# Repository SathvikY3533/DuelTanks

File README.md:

# Duel Tanks
### Two-player real-time tank battle — ECE319H Spring 2026

> Check out more of my work at **[sathvikyechuri.com](https://www.sathvikyechuri.com)**

---

## Demo

📺 *Video coming soon*

---

## Screenshots

| Splash Screen | Tank Select | Gameplay |
|---|---|---|
| *coming soon* | *coming soon* | *coming soon* |

---

## Overview

Duel Tanks is a real-time two-player artillery game built completely from scratch on the MSPM0G3507 microcontroller. Two players face off on separate boards connected by a UART link — shells fired off one screen physically cross over to the opponent's screen, with full parabolic physics preserved across the wire.

Everything — the graphics engine, sprite system, physics engine, UART protocol, sound system, and game state machine — was written from scratch in C++. No game engine, no external libraries.

**Placed 3rd in the ECE319H Spring 2026 in-class competition.**

---

## How It Works

Each board runs the same firmware with a `PLAYER_ID` flag determining which side the player starts on. Missiles exit one screen, get encoded into a 5-byte UART packet, and spawn on the opponent's screen with matching velocity — making it feel like a single continuous battlefield split across two displays.

```
Board 1 (left)          Board 2 (right)
┌──────────────┐        ┌──────────────┐
│   🎯   >>>   │──UART──│   >>> 💥     │
│  [Tank]      │        │       [Tank] │
└──────────────┘        └──────────────┘
     PA8 TX ──────────────► PA22 RX
     PA22 RX ◄────────────── PA8 TX
     GND ◄──────────────────► GND
```

---

## Features

- **Parabolic missile physics** — fixed-point arithmetic, gravity simulation, arc trajectory
- **Cross-screen projectiles** — missiles exit your screen and appear on the opponent's via UART
- **City background** — night skyline with building silhouettes and window lighting
- **Hilly terrain** — multi-sine generated terrain profile, tanks ride the hills
- **3 playable tanks** with unique abilities:
  - 🔵 **Brawler** — Double Shot (fires two missiles spread ±5°)
  - 🟢 **Phantom** — Speed Boost (2× movement speed for 1.5 sec)
  - 🔴 **Artillery** — Ricochet (next shot bounces off terrain)
- **Full game flow** — splash → language select → rules → tank select → battle ready handshake → countdown → gameplay → end screen
- **2-minute match timer** — compare lives at time's up for winner
- **English / Spanish** language support
- **Sound effects** — shoot, explosion, incoming warning, victory, defeat, and more

---

## Hardware

| Component | Details |
|---|---|
| MCU | MSPM0G3507 LaunchPad |
| Display | ST7735R LCD (160×128, landscape) |
| Input | 4 tactile buttons + slide potentiometer |
| Audio | 5-bit R2R DAC → MCP34119P amplifier → speaker |
| Sync | Battle Ready GPIO handshake (PA17 / PA31) |
| Communication | UART at 115200 baud, board-to-board |

### Pin Map
| Signal | Pin |
|---|---|
| LCD SPI | PB6, PB7, PB8, PB9, PB15, PA13 |
| Slide pot (ADC) | PB18 |
| 5-bit DAC | PB0 – PB4 |
| UART TX | PA8 (UART1) |
| UART RX | PA22 (UART2) |
| Battle Ready Out | PA17 (P1) / PA31 (P2) |
| Battle Ready In | PA31 (P1) / PA17 (P2) |
| Fire button | PB17 |
| Shield button | PB12 |
| Left button | PB16 |
| Right button | PA27 |

---

## Software Architecture

```
main5.cpp
└── Game_Update()          ← called every 33ms (30Hz)
    ├── Switch_Tick()      ← edge detection for all 4 buttons
    ├── State machine      ← SPLASH → LANGUAGE → RULES → TANK_SELECT
    │                         → WAITING → COUNTDOWN → GAMEPLAY → END
    ├── Physics engine     ← fixed-point parabolic missile simulation
    ├── Sprite renderer    ← transparent pixel-by-pixel draw, dirty-rect erase
    ├── GameUART           ← 5-byte packets with 0xAA 0x55 sync header
    └── Sound engine       ← SysTick ISR at 11025Hz → R2R DAC output
```

### UART Packet Format
```
[ 0xAA ][ 0x55 ][ TYPE ][ DATA1 ][ DATA2 ]
  sync    sync    what    payload  payload
```

---

## Controls

| Input | Action |
|---|---|
| Left / Right buttons | Move tank |
| Slide pot | Aim angle (0° – 89°) |
| Hold Fire | Charge shot power |
| Release Fire | Shoot |
| Shield | Use tank ability |
| Fire + Left + Right (hold) | Force quit match |

---

## Building

Open in Code Composer Studio with the ECE319H Lab 9 starter project. Add all `.cpp` / `.h` files. Before flashing:

1. Set `#define PLAYER_ID 1` in `Game.h` for the left board
2. Set `#define PLAYER_ID 2` in `Game.h` for the right board
3. Connect boards: PA8→PA22, PA22→PA8, GND→GND

---

## License

Built for ECE319H at UT Austin. All game logic, physics, graphics, and UART protocol written from scratch.

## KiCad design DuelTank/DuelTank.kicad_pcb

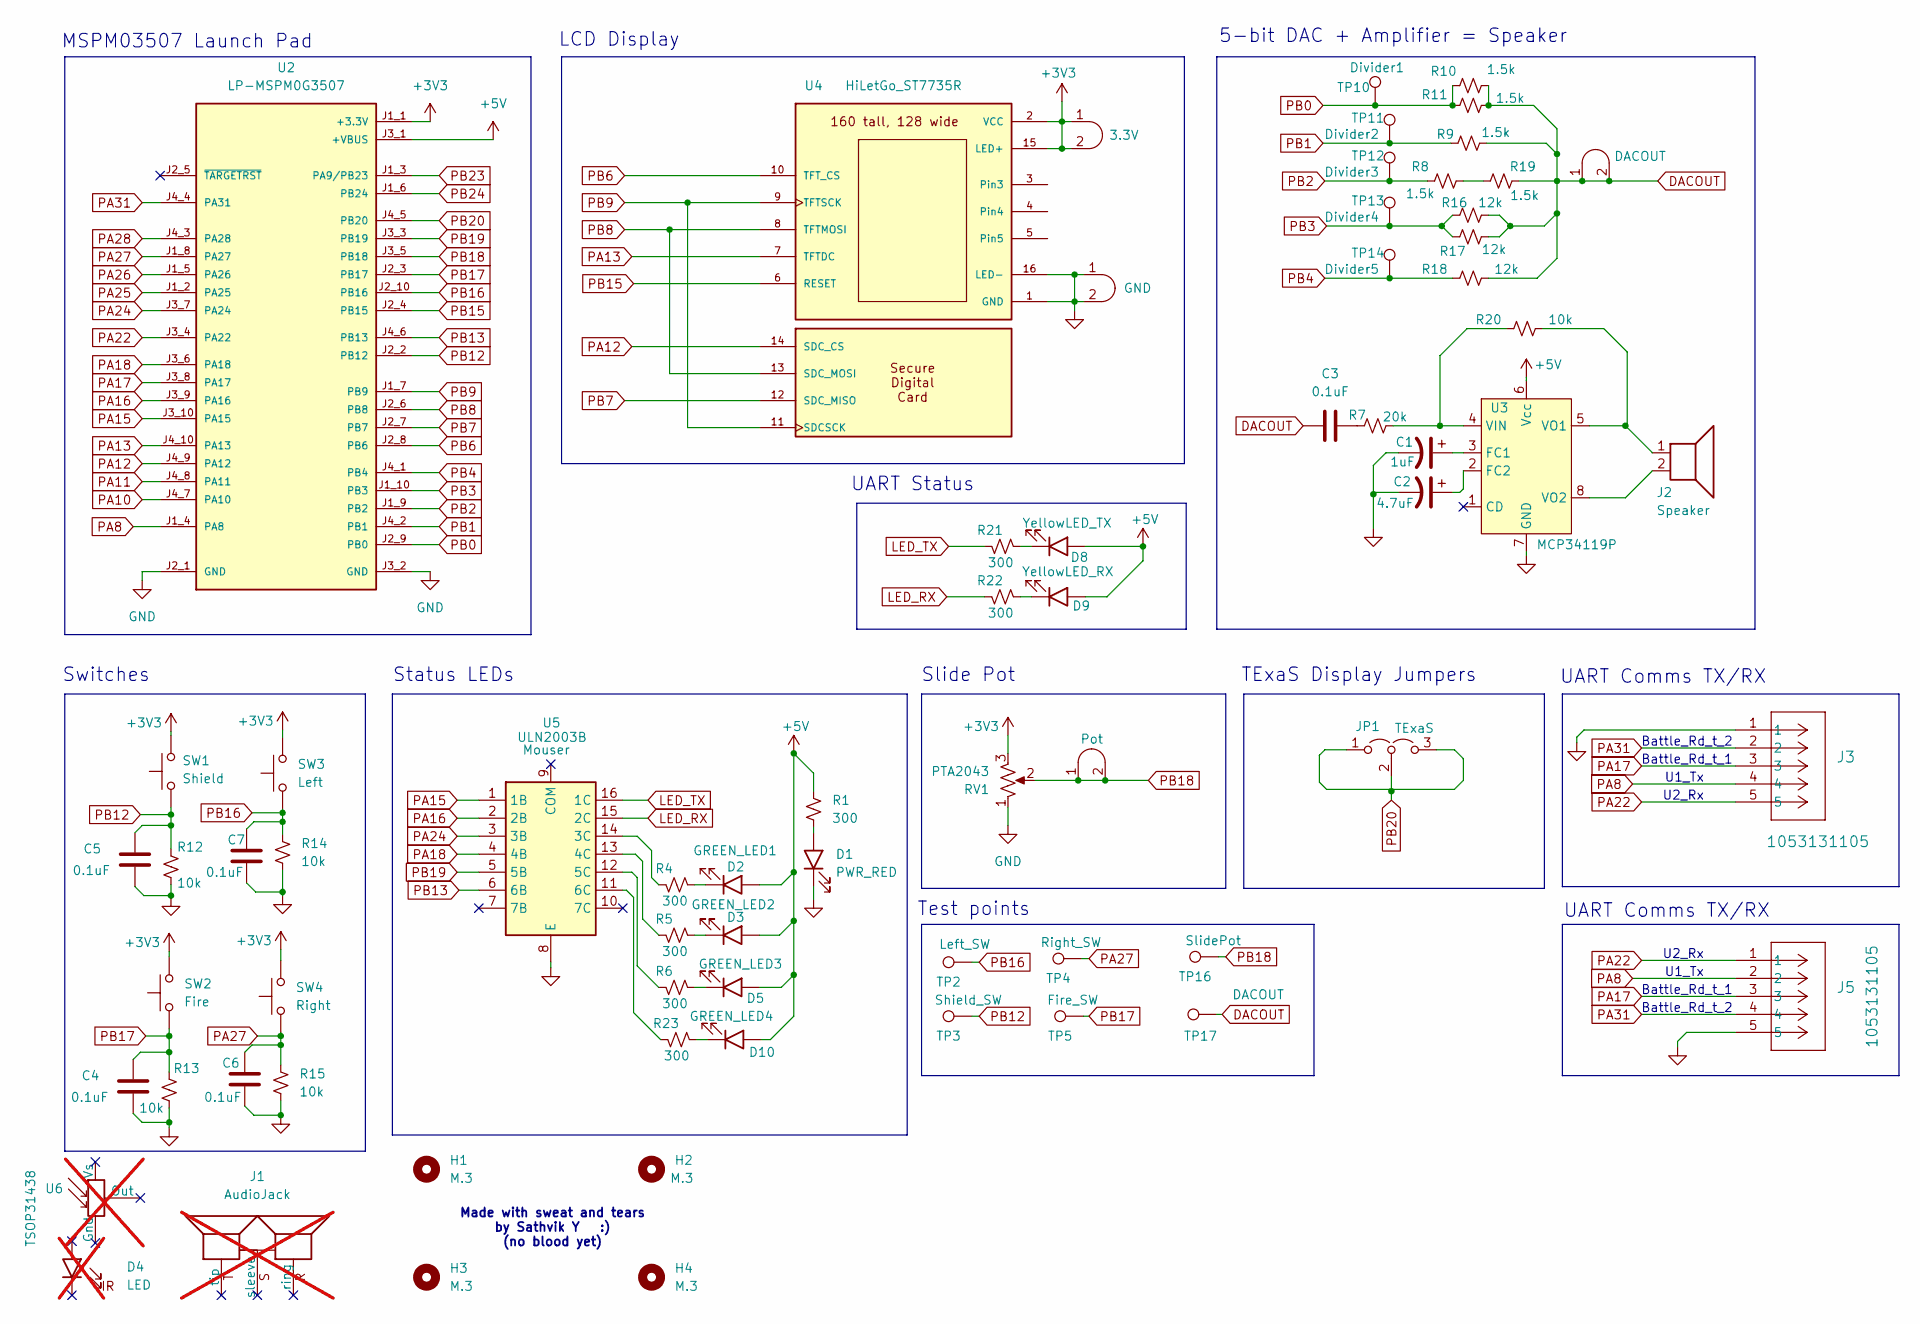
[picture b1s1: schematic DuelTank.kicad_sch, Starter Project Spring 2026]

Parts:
C1: 1uF; CP_Radial_Tantal200mil
C2: 4.7uF; CP_Radial_Tantal200mil
C3, C4, C5, C6, C7: 0.1uF; C_Axial_200mil
D1: PWR_RED; LED_D5.0mm
D2: GREEN_LED1; LED_D5.0mm
D3: GREEN_LED2; LED_D5.0mm
D4: LED; LED_D5.0mm; not fitted
D5: GREEN_LED3; LED_D5.0mm
D8: YellowLED_TX; LED_D5.0mm
D9: YellowLED_RX; LED_D5.0mm
D10: GREEN_LED4; LED_D5.0mm
H1, H2, H3, H4: M.3; MountingHole_3.2mm_M3_Pad_TopBottom
J1: AudioJack; Jack_3.5mm_CUI_SJ1-3523N_Horizontal; not fitted
J2: Speaker; PinHeader_1x02_P2.54mm_Vertical
J3, J5: 1053131105; CONN_SD-105313-100_05_MOL
J4: Pot; Testpoint_1x02_P2.54mm
J6: GND; Testpoint_1x02_P2.54mm
J7: DACOUT; Testpoint_1x02_P2.54mm
JP1: TExaS; PinHeader_1x03_P2.54mm_Vertical
R1, R4, R5, R6, R21, R22, R23: 300; R_Axial_DIN0204_L3.6mm_D1.6mm_P7.62mm_Horizontal
R7: 20k; R_Axial_DIN0204_L3.6mm_D1.6mm_P7.62mm_Horizontal
R8, R9, R10, R11, R19: 1.5k; R_Axial_DIN0204_L3.6mm_D1.6mm_P7.62mm_Horizontal
R12, R13, R14, R15, R20: 10k; R_Axial_DIN0204_L3.6mm_D1.6mm_P7.62mm_Horizontal
R16, R17, R18: 12k; R_Axial_DIN0204_L3.6mm_D1.6mm_P7.62mm_Horizontal
RV1: PTA2043; PTA2043pot
SW1: Shield; SW_PUSH_6mm
SW2: Fire; SW_PUSH_6mm
SW3: Left; SW_PUSH_6mm
SW4: Right; SW_PUSH_6mm
TP1: 3.3V; Testpoint_1x02_P2.54mm
TP2: Left_SW; TestPoint_Pad_D2.0mm
TP3: Shield_SW; TestPoint_Pad_D2.0mm
TP4: Right_SW; TestPoint_Pad_D2.0mm
TP5: Fire_SW; TestPoint_Pad_D2.0mm
TP10: Divider1; TestPoint_Pad_D2.0mm
TP11: Divider2; TestPoint_Pad_D2.0mm
TP12: Divider3; TestPoint_Pad_D2.0mm
TP13: Divider4; TestPoint_Pad_D2.0mm
TP14: Divider5; TestPoint_Pad_D2.0mm
TP16: SlidePot; TestPoint_Pad_D2.0mm
TP17: DACOUT; TestPoint_Pad_D2.0mm
U2: LP-MSPM0G3507; ti_LP_MSPM0G3507
U3: MCP34119P; DIP-8_W7.62mm_LongPads
U4: HiLetGo_ST7735R; hiletgo_st7735r
U5: ULN2003B; DIP-16_W7.62mm
U6: TSOP31438; not fitted

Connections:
+3V3: RV1.3, SW1.2, SW2.2, SW3.2, SW4.2, TP1.1 (A), TP1.2 (B), U2.J1_1 (+3.3V), U4.2 (VCC), U4.15 (LED+); also elsewhere on the board
+5V: D2.2 (A), D3.2 (A), D5.2 (A), D8.2 (A), D9.2 (A), D10.2 (A), R1.1, U2.J3_1 (+VBUS), U3.6 (Vcc)
DACOUT: C3.1, J7.1 (A), J7.2 (B), R9.1, R10.1, R11.1, R16.1, R17.1, R18.1, R19.1, TP17.1
GND: C1.2, C2.2, C4.1, C5.1, C6.1, C7.1, D1.1 (K), J3.1, J5.5, J6.1 (A), J6.2 (B), R12.2, R13.2, R14.2, R15.2, RV1.1, U2.J2_1 (GND), U2.J3_2 (GND), U3.7 (GND), U4.1 (GND), U4.16 (LED-), U5.8 (E); also elsewhere on the board
LED_RX: R22.2, U5.15 (2C)
LED_TX: R21.2, U5.16 (1C)
unnamed: C3.2, R7.2
unnamed: D1.2 (A), R1.2
unnamed: D2.1 (K), R4.1
unnamed: D3.1 (K), R5.1
unnamed: D5.1 (K), R6.1
unnamed: D8.1 (K), R21.1
unnamed: D9.1 (K), R22.1
unnamed: D10.1 (K), R23.1
unnamed: R8.1, R19.2
unnamed: C1.1, U3.3 (FC1)
unnamed: C2.1, U3.2 (FC2)
unnamed: R7.1, R20.2, U3.4 (VIN)
unnamed: J2.1, R20.1, U3.5 (VO1)
unnamed: J2.2, U3.8 (VO2)
unnamed: R4.2, U5.14 (3C)
unnamed: R5.2, U5.13 (4C)
unnamed: R6.2, U5.12 (5C)
unnamed: R23.2, U5.11 (6C)
PA8: J3.4, J5.2, U2.J1_4 (PA8)
PA10: U2.J4_7 (PA10)
PA11: U2.J4_8 (PA11)
PA12: U2.J4_9 (PA12), U4.14 (SDC_CS)
PA13: U2.J4_10 (PA13), U4.7 (TFTDC); also elsewhere on the board
PA15: U2.J3_10 (PA15), U5.1 (1B)
PA16: U2.J3_9 (PA16), U5.2 (2B)
PA17: J3.3, J5.3, U2.J3_8 (PA17)
PA18: U2.J3_6 (PA18), U5.4 (4B)
PA22: J3.5, J5.1, U2.J3_4 (PA22)
PA24: U2.J3_7 (PA24), U5.3 (3B)
PA25: U2.J1_2 (PA25)
PA26: U2.J1_5 (PA26)
PA27: C6.2, R15.1, SW4.1, TP4.1, U2.J1_8 (PA27)
PA28: U2.J4_3 (PA28)
PA31: J3.2, J5.4, U2.J4_4 (PA31)
PB0: R10.2, R11.2, TP10.1, U2.J2_9 (PB0)
PB1: R9.2, TP11.1, U2.J4_2 (PB1)
PB2: R8.2, TP12.1, U2.J1_9 (PB2)
PB3: R16.2, R17.2, TP13.1, U2.J1_10 (PB3)
PB4: R18.2, TP14.1, U2.J4_1 (PB4)
PB6: U2.J2_8 (PB6), U4.10 (TFT_CS); also elsewhere on the board
PB7: U2.J2_7 (PB7), U4.12 (SDC_MISO)
PB8: U2.J2_6 (PB8), U4.8 (TFTMOSI), U4.13 (SDC_MOSI); also elsewhere on the board
PB9: U2.J1_7 (PB9), U4.9 (TFTSCK), U4.11 (SDCSCK); also elsewhere on the board
PB12: C5.2, R12.1, SW1.1, TP3.1, U2.J2_2 (PB12)
PB13: U2.J4_6 (PB13), U5.6 (6B)
PB15: U2.J2_4 (PB15), U4.6 (RESET); also elsewhere on the board
PB16: C7.2, R14.1, SW3.1, TP2.1, U2.J2_10 (PB16)
PB17: C4.2, R13.1, SW2.1, TP5.1, U2.J2_3 (PB17)
PB18: J4.1 (A), J4.2 (B), RV1.2, TP16.1, U2.J3_5 (PB18)
PB19: U2.J3_3 (PB19), U5.5 (5B)
PB20: JP1.1 (A), JP1.2 (C), JP1.3 (B), U2.J4_5 (PB20)
PB23: U2.J1_3 (PA9/PB23)
PB24: U2.J1_6 (PB24)

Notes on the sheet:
Battle_Rd_t_1
LCD Display
U1_Tx
Battle_Rd_t_2
U2_Rx
5-bit DAC + Amplifier = Speaker
TExaS Display Jumpers
Slide Pot
Test points
Switches
Status LEDs
MSPM03507 Launch Pad
UART Comms TX/RX
Made with sweat and tears by Sathvik Y :) (no blood yet)
UART Status

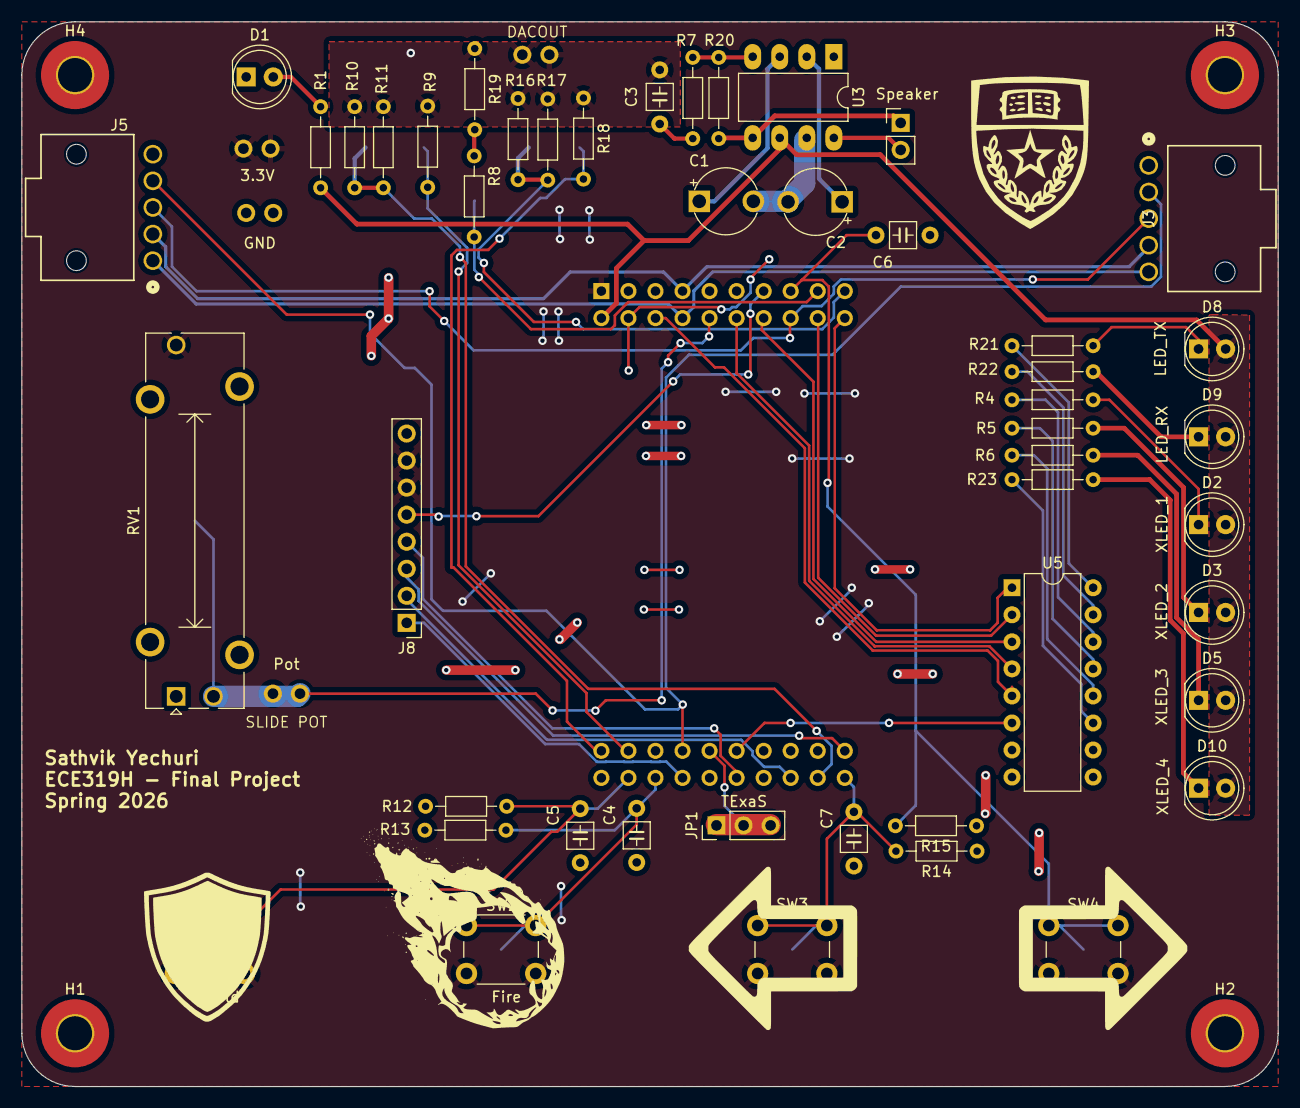
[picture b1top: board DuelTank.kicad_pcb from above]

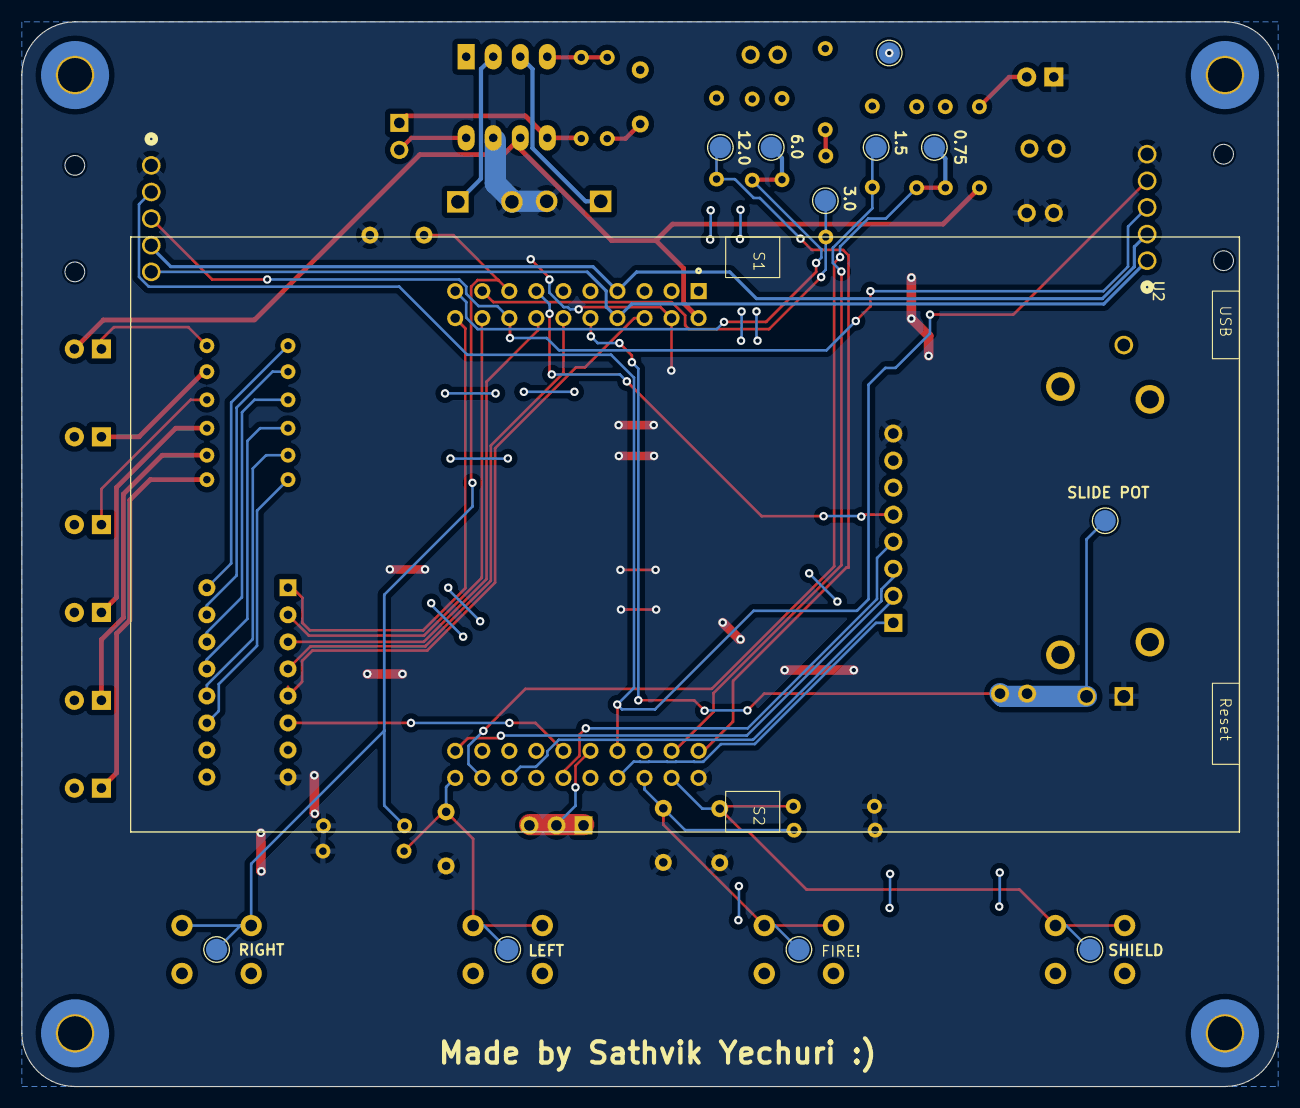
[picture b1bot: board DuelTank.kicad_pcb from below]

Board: 2 copper layers, 118.0 x 100.0 mm, 67 parts (12 on the bottom side), 50 nets.

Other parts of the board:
J8: Conn_01x08; PinHeader_1x08_P2.54mm_Vertical

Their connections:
+3V3: J8.6, J8.7; also elsewhere on the board
GND: J8.8; also elsewhere on the board
PA13: J8.3; also elsewhere on the board
PB6: J8.2; also elsewhere on the board
PB8: J8.4; also elsewhere on the board
PB9: J8.5; also elsewhere on the board
PB15: J8.1; also elsewhere on the board

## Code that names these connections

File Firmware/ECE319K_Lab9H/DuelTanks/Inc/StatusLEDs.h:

// Switch.h
// Duel Tanks - LED driver

// ECE319H Spring 2026

#ifndef STATUS_LEDS_H
#define STATUS_LEDS_H

#include <stdint.h>
#include <stdbool.h>
#include "../inc/LaunchPad.h"


#define LED_RX   (1U << 16)  // PA16
#define LED_TX   (1U << 15)  // PA15
#define X_LED1   (1U << 24)  // PA24
#define X_LED2   (1U << 18)  // PA18
#define X_LED3   (1U << 19)  // PB19
#define X_LED4   (1U << 13)  // PB13

void StatusLEDs_Init(void);

void led_toggle(uint32_t led_mask);

#endif

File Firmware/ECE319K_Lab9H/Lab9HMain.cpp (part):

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    PLL_Init();          // 80 MHz
    LaunchPad_Init();    // GPIO, ports A and B
    GFX_Init();          // LCD landscape 160x128
    Switch_Init();       // PB12 PB16 PB17 PA27
    Sound_Init();        // SysTick + DAC at 11025 Hz
    GameUART_Init();     // UART1 TX PA8, UART2 RX PA22
    Sensor.Init();       // ADC for slide pot PB18
    __enable_irq();

    Game_Init();         // draws splash screen, sets up state machine
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  LaunchPad_Init();
  GFX_Init();

  // Sensor.Init(); // PB18 = ADC1 channel 5, slidepot
  // Switch_Init(); // initialize switches
  // LED_Init();    // initialize LED
  // Sound_Init();  // initialize sound
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  LaunchPad_Init();
  GFX_Init();
  Switch_Init();
  Sensor.Init(); // PB18 = ADC1 ch5, slide pot
  __enable_irq();

  // ---- Draw static labels (only once) ----
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//   Switch_Init();          // initialize switches
//   LED_Init();             // initialize LED
//   Sound_Init();           // initialize sound
//   TExaS_Init(ADC0, 6, 0); // ADC1 channel 6 is PB20, TExaS scope
//   __enable_irq();
//   while (1) {
//     now = Switch_In(); // one of your buttons
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//   ST7735_InitPrintf(
//       INITR_REDTAB); // INITR_REDTAB for AdaFruit, INITR_BLACKTAB for HiLetGo
//   ST7735_FillScreen(ST7735_BLACK);
//   Sensor.Init(); // PB18 = ADC1 channel 5, slidepot
//   Switch_Init(); // initialize switches
//   LED_Init();    // initialize LED
//   Sound_Init();  // initialize sound
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
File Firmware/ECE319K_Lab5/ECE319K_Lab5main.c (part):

/* ECE319K_Lab5main.c
 * Digital Piano using a Digital to Analog Converter
 * January 12, 2026
 * 5-bit binary-weighted DAC connected to PB4-PB0
 * 4-bit keyboard connected to PB19-PB16
*/

#include <ti/devices/msp/msp.h>
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  }
}
// use main2b to perform static testing of DAC, if you do not have a voltmeter
// attach PB20 (scope uses PB20 as ADC input) to your DACout
// TExaSdisplay scope uses TimerG7, ADC0
// To use the scope, there can be no breakpoints in your code
int main2b(void){ // main2b
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}
// use main3 to perform dynamic testing of DAC,
// In lab, attach your DACout to the real scope
// If you do not have a scope attach PB20 (scope uses PB20 as ADC input) to your DACout
// TExaSdisplay scope uses TimerG7, ADC0
// To perform dynamic testing, there can be no breakpoints in your code
// DACout will be a monotonic ramp with period 32ms,
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
// use main5 to debug your system
// In lab, attach your DACout to the real scope
// If you do not have a scope attach PB20 (scope uses PB20 as ADC input) to your DACout
// TExaSdisplay scope uses TimerG7, ADC0
// To perform dynamic testing, there can be no breakpoints in your code
// DACout will be a sine wave with period/frequency depending on which key is pressed
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uint32_t last,key;
// use main6 to debug/grade your final system
// In lab, attach your DACout to the real scope
// If you do not have a scope attach PB20 (scope uses PB20 as ADC input) to your DACout
// TExaSdisplay scope uses TimerG7, ADC0
// To perform dynamic testing, there can be no breakpoints in your code
// DACout will be a sine wave with period/frequency depending on which key is pressed
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    Clock_Delay(800000); // 10ms, to debounce switch
  }
}
// To grade you must connect PB20 to your DACout
// Run main5 with Lab5Grader(3);   // Grader
// Observe Terminal window

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
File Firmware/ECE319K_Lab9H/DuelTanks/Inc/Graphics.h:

// Graphics.h
// Duel Tanks - wrapper func for ST7735 Display
// ST7735 in landscape mode (160x128)
// LCD pins from schematic: PB15(CS) PB6(DC) PA13(RST) PB8(SCK) PB9(MOSI)
// Author: Sathvik
// ECE319H Spring 2026

#ifndef GRAPHICS_H
#define GRAPHICS_H

#include <stdint.h>
#include <stdbool.h>

// screen size
#define SCREEN_W        160
#define SCREEN_H        128

// HUD rect strips - to prevent from entire screen from refreshing
#define HUD_TOP_H       14      // pixels tall: lives + kills strip
#define HUD_BOT_H       10      // pixels tall: cooldown bar strip
#define PLAY_Y_MIN      HUD_TOP_H
#define PLAY_Y_MAX      (SCREEN_H - HUD_BOT_H - 1)
#define PLAY_H          (SCREEN_H - HUD_TOP_H - HUD_BOT_H)

// colors!
#define COLOR_BLACK       ((uint16_t)0x0000)
#define COLOR_WHITE       ((uint16_t)0xFFFF)
#define COLOR_RED         ((uint16_t)0xF800)
#define COLOR_GREEN       ((uint16_t)0x07E0)
#define COLOR_BLUE        ((uint16_t)0x001F)
#define COLOR_YELLOW      ((uint16_t)0xFFE0)
#define COLOR_CYAN        ((uint16_t)0x07FF)
#define COLOR_MAGENTA     ((uint16_t)0xF81F)
#define COLOR_ORANGE      ((uint16_t)0xFC60)
#define COLOR_DARKGRAY    ((uint16_t)0x39E7)
#define COLOR_LIGHTGRAY   ((uint16_t)0xC618)
#define COLOR_DARKGREEN   ((uint16_t)0x03E0)
#define COLOR_GOLD        ((uint16_t)0xFEA0)
#define COLOR_BACKGROUND  ((uint16_t)0x0841)  // dark blue-gray battlefield

// ================================================================
// Sprite struct — enables "hit box" to prevent screen flicker
//
// only redraws when 'dirty' is true - meaning state of sprite has changed
// ================================================================
typedef struct {
    int16_t         x;          // current x (top-left)
    int16_t         y;          // current y (top-left)
    int16_t         prevX;      // previous x for erase
    int16_t         prevY;      // previous y for erase
    uint8_t         w;          // width  in pixels
    uint8_t         h;          // height in pixels
    bool            visible;    // false = skip draw (cloak ability)
    bool            dirty;      // true = needs redraw
    const uint16_t* bitmap;     // RGB565 pixel array, row-major
} Sprite_t;

// GFX init
void GFX_Init(void);

// color entire screen
void GFX_FillScreen(uint16_t color);

// Clears non-hud area (using the HUD strips above)
void GFX_ClearPlayArea(void);

// basic shape shi
void GFX_FillRect(int16_t x, int16_t y, int16_t w, int16_t h, uint16_t color);
void GFX_DrawRect(int16_t x, int16_t y, int16_t w, int16_t h, uint16_t color);
void GFX_DrawPixel(int16_t x, int16_t y, uint16_t color);
void GFX_DrawLine(int16_t x0, int16_t y0, int16_t x1, int16_t y1, uint16_t color);
void GFX_DrawCircle(int16_t cx, int16_t cy, int16_t r, uint16_t color);
void GFX_FillCircle(int16_t cx, int16_t cy, int16_t r, uint16_t color);

// Texst stuff
void GFX_DrawChar(int16_t x, int16_t y, char c,
                  uint16_t color, uint16_t bg, uint8_t size);
void GFX_DrawString(int16_t x, int16_t y, const char* str,
                    uint16_t color, uint16_t bg, uint8_t size);

// special string out for splash screens
void GFX_DrawStringCentered(int16_t y, const char* str,
                             uint16_t color, uint16_t bg, uint8_t size);

// fixed point helper func
void GFX_DrawInt(int16_t x, int16_t y, int32_t val,
                 uint16_t color, uint16_t bg, uint8_t size);




// Initialize a sprite. Sets prevX/prevY = x/y, dirty = true, visible = true
void GFX_SpriteInit(Sprite_t* s,
                    int16_t x, int16_t y,
                    uint8_t w, uint8_t h,
                    const uint16_t* bitmap);

// Update position — stores new coords, marks dirty (meaning need redraw)
void GFX_SpriteMove(Sprite_t* s, int16_t newX, int16_t newY);

// Main draw call — erases old position, draws at new position
// Only acts if dirty == true and visible == true - prevent from unneccesary processing
void GFX_SpriteDraw(Sprite_t* s);

// Erase sprite at current position
void GFX_SpriteErase(Sprite_t* s);

// Force a full redraw even if dirty == false (debugging - it works now!!!)
void GFX_SpriteForceRedraw(Sprite_t* s);

// Swap bitmap (mostly for animating the aim line)
void GFX_SpriteSetBitmap(Sprite_t* s, const uint16_t* newBitmap);


// GFX_DrawHUD = draw the full HUD + helper funcs to update HUD values
void GFX_DrawHUD(uint8_t lives, uint8_t kills, uint8_t cooldownPct);
void GFX_UpdateLives(uint8_t lives);          // redraws lives section only
void GFX_UpdateKills(uint8_t kills);          // redraws kills section only
void GFX_UpdateCooldownBar(uint8_t pct);      // 0=empty, 100=full


//flash entire screen for a very short time - used for shoig damage taken
void GFX_FlashScreen(uint16_t color, uint8_t numFrames);

// Explosion BOOOOM
void GFX_DrawExplosionFrame(int16_t cx, int16_t cy, uint8_t frame);

// Explosion bye :(
void GFX_EraseExplosion(int16_t cx, int16_t cy);

// INCOMING! warning - top right of screen
void GFX_DrawIncoming(void);
void GFX_ClearIncoming(void);

// Charge bar stuff for shooting shots
void GFX_DrawChargeBar(int16_t x, int16_t y, uint8_t pct);
void GFX_EraseChargeBar(int16_t x, int16_t y);

// screen shaking effects
void GFX_ShakeStart(int8_t intensity);
void GFX_ShakeTick(void);                    // call once per game frame
int8_t GFX_ShakeOffsetX(void);              // add to all x coords during shake
int8_t GFX_ShakeOffsetY(void);              // add to all y coords during shake




// --- Splash screens ------------------------------------------

// Each function does a full screen redraw — only call on state transitions

// Splash screen helper func
void GFX_DrawSplash(bool showPrompt);

// Language select helper func
void GFX_DrawLanguageSelect(uint8_t sel);

// Rules pages helper func
void GFX_DrawRulesPage(uint8_t page, uint8_t lang);

// Tank select helper func
void GFX_DrawTankSelect(uint8_t sel, int8_t oppSel, bool oppReady, uint8_t lang);

// Waiting for oppon screen func
void GFX_DrawWaiting(uint8_t dotFrame, uint8_t lang);

// Countdown and then FIGHT! screen transition
void GFX_DrawCountdown(uint8_t n);

// End screen - vicotry/defeat screen
void GFX_DrawEndScreen(bool won, uint8_t myKills, uint8_t lang);

// Rematch prompt screen
void GFX_DrawRematch(uint8_t lang);

#endif // GRAPHICS_H

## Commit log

2026-04-06 readme msg init
    Updated project title and added a brief description.
2026-04-06 we cookin
2026-04-06 read me specification //todo
2026-04-11 sch init
2026-04-14 hardware done
2026-04-14 .lck file fix
2026-04-15 board ordered!
2026-04-25 firmware done
2026-04-25 :)
    Updated project details and added comprehensive sections on gameplay, features, hardware, software architecture, controls, and building instructions.
